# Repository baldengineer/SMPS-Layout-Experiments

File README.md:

## SMPS Layout Experiments (with a MC34167)

There are four different layouts:
1. Autorouted. The parts were how KiCad placed them in pcbnew and then FreeRoute routed it.
2. 6 mil. The parts were layed out logically (and functionally). Traces were set to OSHPark's minimum and then routed manually.
3. 6 mil w/ plane. Same design as #2 but the bottom layer is designed as a ground plane.
4. Well-designed. (Hopefully) a correct design. Instead of traces, this design relies on copper "pours" to connect the critical nets.

## Bald Engineer Live Stream
Watch the stream and help out in chat here:
https://twitch.tv/baldengineer

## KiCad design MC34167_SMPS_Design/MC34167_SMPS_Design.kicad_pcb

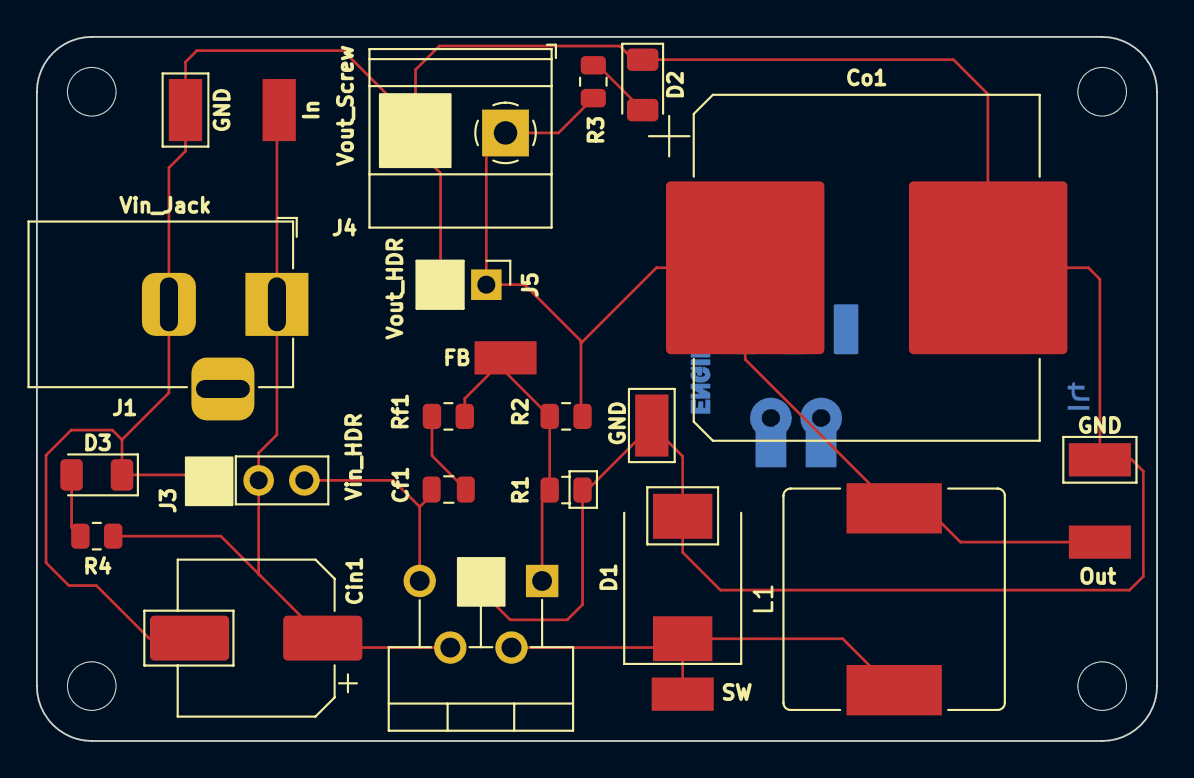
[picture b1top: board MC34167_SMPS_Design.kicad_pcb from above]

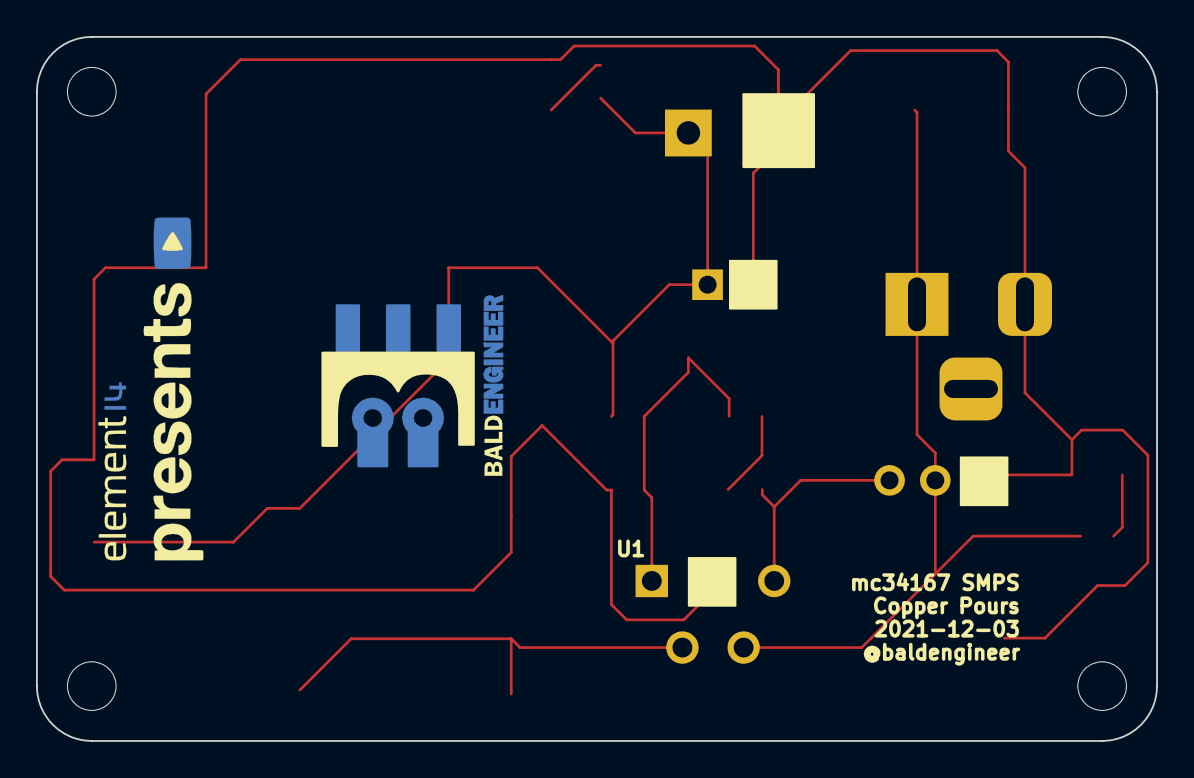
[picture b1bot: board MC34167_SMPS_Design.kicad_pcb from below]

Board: 2 copper layers, 62.2 x 39.1 mm, 30 parts (2 on the bottom side), 9 nets.

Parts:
Cf1: 100n; C_0805_2012Metric
Cin1: 300u; CP_Elec_8x10.5
Co1: 4700u; CP_Elec_18x17.5
D1: 50V,5A; D_SMC
D2: Vout; LED_1206_3216Metric
D3: Vin; LED_1206_3216Metric
H1, H2, H3, H4: MountingHole; MountingHole_2.7mm_M2.5
J1: Vin_Jack; BarrelJack_Horizontal
J3: Vin_HDR; PinHeader_1x03_P2.54mm_Vertical
J4: Vout_Screw; TerminalBlock_Phoenix_MKDS-1,5-2_1x02_P5.00mm_Horizontal
J5: Vout_HDR; PinHeader_1x02_P2.54mm_Vertical
L1: 180u; L_Bourns_SRR1210A
R1, R3, R4: k; R_0805_2012Metric
R2: 6.8k; R_0805_2012Metric
Ref**: Val**; e14presents logo 20mm silk and copper v1
Rf1: 68k; R_0805_2012Metric
TP1: In; Harwin-S1751-46-Test-Point
TP2: FB; Harwin-S1751-46-Test-Point
TP3: SW; Harwin-S1751-46-Test-Point
TP4: Out; Harwin-S1751-46-Test-Point
TP5, TP6, TP7: GND; Harwin-S1751-46-Test-Point
U1: MC34167; TO-220-5_P3.4x3.7mm_StaggerOdd_Lead3.8mm_Vertical
svg2mod: G***; BE10v2

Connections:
/Comp: Cf1.1, J3.3, U1.5
/Fb: R1.1, R2.2, Rf1.1, TP2.1, U1.1
/SW: D1.1, L1.1, TP3.1, U1.2
/Vin: Cin1.1, J1.1, J3.2, R4.1, TP1.1, U1.4
/Vout: Co1.1, J4.1, J5.1, L1.2, R2.1, R3.1, TP4.1
GND: Cin1.2, Co1.2, D1.2, D2.1, D3.1, J1.2, J3.1, J4.2, J5.2, R1.2, TP5.1, TP6.1, TP7.1, U1.3
unnamed: Cf1.2, Rf1.2
unnamed: D2.2, R3.2
unnamed: D3.2, R4.2

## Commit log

2021-12-26 the files ... :)
